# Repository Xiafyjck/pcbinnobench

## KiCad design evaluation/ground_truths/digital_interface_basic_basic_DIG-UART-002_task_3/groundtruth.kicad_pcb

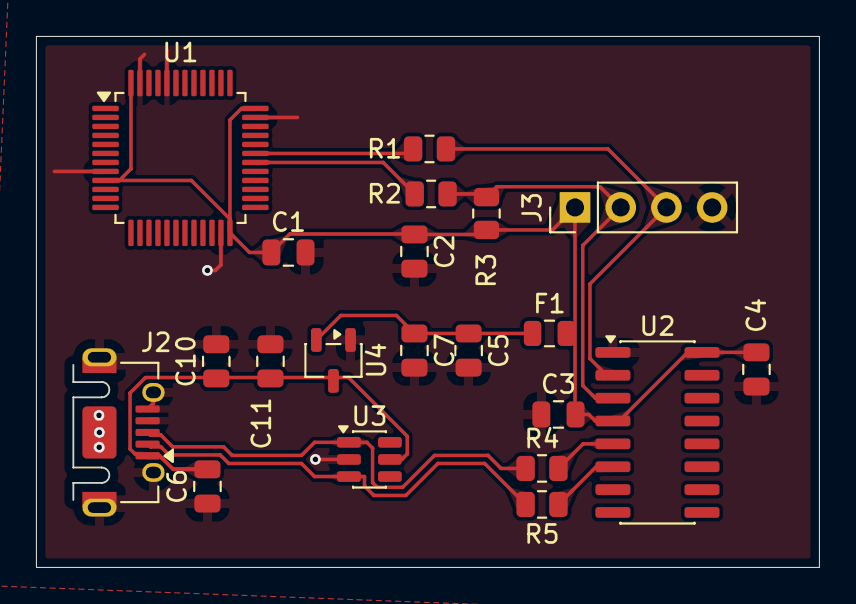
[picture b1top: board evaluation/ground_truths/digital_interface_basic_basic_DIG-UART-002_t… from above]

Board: 2 copper layers, 43.5 x 29.5 mm, 21 parts (0 on the bottom side), 12 nets.

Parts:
C1: 0.1uf; C_0805_2012Metric
C2: 1uf; C_0805_2012Metric
C3, C4, C7, C11: 100nf; C_0805_2012Metric
C5, C6, C10: 10uf; C_0805_2012Metric
F1: Polyfuse; Fuse_0805_2012Metric
J2: USB_B_Micro; USB_Micro-AB_Molex_47590-0001
J3: Conn_01x04_Pin; PinHeader_1x04_P2.54mm_Vertical
R1, R2: 50; R_0805_2012Metric
R3: 10k; R_0805_2012Metric
R4, R5: 22; R_0805_2012Metric
U1: STM32F103C8Tx; LQFP-48_7x7mm_P0.5mm
U2: CH340C; SOIC-16_3.9x9.9mm_P1.27mm
U3: SRV05-4; SOT-23-6
U4: XC6206PxxxMR; SOT-23-3

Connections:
+3V3: C1.1, C2.1, C3.2, C4.2, F1.2, J3.1, R3.2, U1.9 (VDDA), U1.24 (VDD), U1.36 (VDD), U1.48 (VDD), U2.4 (V3), U2.16 (VCC)
+5V: C6.2, C10.1, C11.1, J2.1 (VBUS), U3.5 (VP), U4.3 (VI)
/usb-uart/D+: J2.3 (D+), R4.1, U3.1 (IO1)
/usb-uart/D-: J2.2 (D-), R5.2, U3.3 (IO2)
/usb-uart/RX: J3.2, R2.2, R3.1, U2.3 (RXD)
/usb-uart/TX: J3.3, R1.2, U2.2 (TXD)
GND: C1.2, C2.2, C3.1, C4.1, C5.2, C6.1, C7.2, C10.2, C11.2, J2.4 (ID), J2.5 (GND), J2.6 (Shield), J3.4, U1.8 (VSSA), U1.23 (VSS), U1.35 (VSS), U1.44 (BOOT0), U1.47 (VSS), U2.1 (GND), U3.2 (VN), U4.1 (GND)
unnamed: R2.1, U1.30 (PA9)
unnamed: R1.1, U1.31 (PA10)
unnamed: R4.2, U2.5 (UD+)
unnamed: R5.1, U2.6 (UD-)
unnamed: C5.1, C7.1, F1.1, U4.2 (VO)

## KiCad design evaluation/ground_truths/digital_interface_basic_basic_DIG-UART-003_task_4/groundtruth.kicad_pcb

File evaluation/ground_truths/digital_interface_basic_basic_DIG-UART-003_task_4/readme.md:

# Cross-Voltage Domain UART Interface Board

This directory contains KiCad reference project, datasheets, and fault localization tasks for the cross-voltage domain UART interface board.

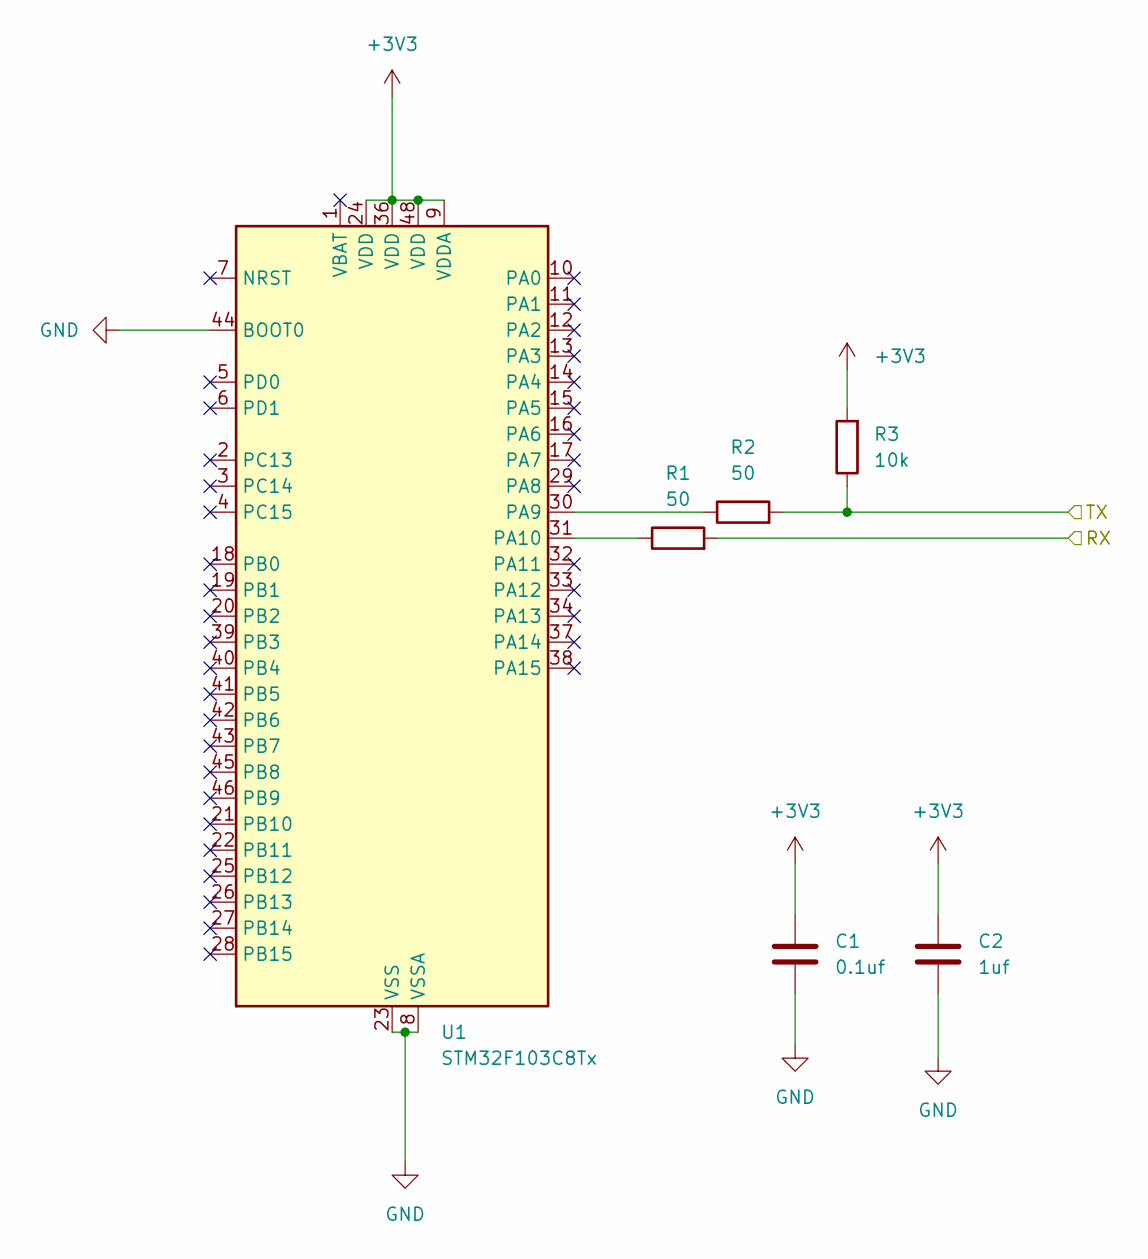
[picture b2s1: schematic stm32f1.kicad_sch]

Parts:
C1: 0.1uf; C_0805_2012Metric
C2: 1uf; C_0805_2012Metric
R1, R2: 50; R_0805_2012Metric
R3: 10k; R_0805_2012Metric
U1: STM32F103C8Tx; LQFP-48_7x7mm_P0.5mm

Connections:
+3V3: C1.1, C2.1, R3.2, U1.9 (VDDA), U1.24 (VDD), U1.36 (VDD), U1.48 (VDD); also elsewhere on the board
/stm32-uart/RX: R1.2; also elsewhere on the board
/stm32-uart/TX: R2.2, R3.1; also elsewhere on the board
GND: C1.2, C2.2, U1.8 (VSSA), U1.23 (VSS), U1.35 (VSS), U1.44 (BOOT0), U1.47 (VSS); also elsewhere on the board
unnamed: R2.1, U1.30 (PA9)
unnamed: R1.1, U1.31 (PA10)

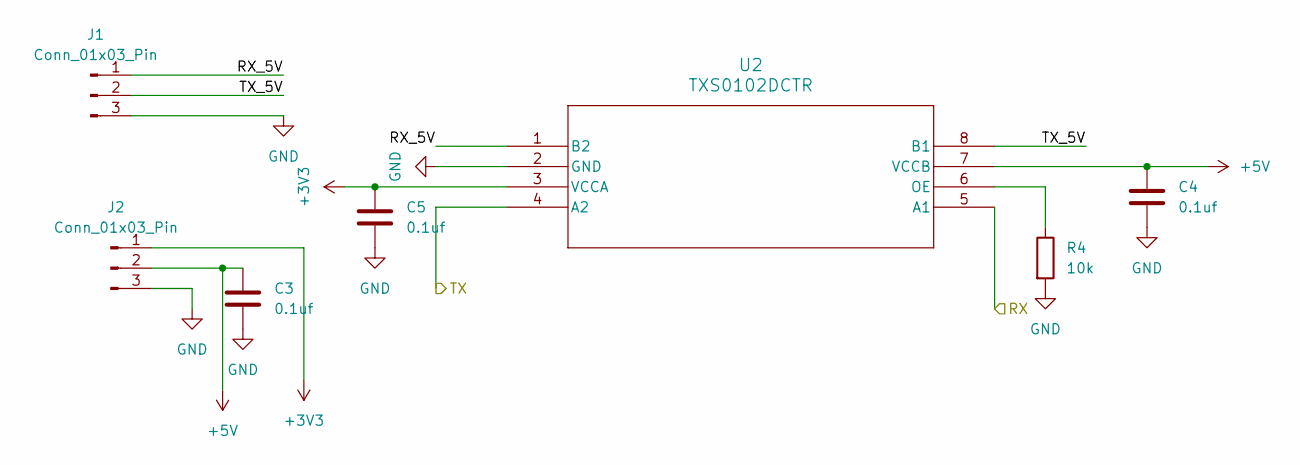
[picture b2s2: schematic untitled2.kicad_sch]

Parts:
C3, C4, C5: 0.1uf; C_0805_2012Metric
J1, J2: Conn_01x03_Pin; PinHeader_1x03_P2.54mm_Vertical
R4: 10k; R_0805_2012Metric
U2: TXS0102DCTR; DCT8

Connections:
+3V3: C5.1, J2.1, U2.3 (VCCA); also elsewhere on the board
+5V: C3.1, C4.1, J2.2, U2.7 (VCCB)
/stm32-uart/RX: U2.4 (A2); also elsewhere on the board
/stm32-uart/TX: U2.5 (A1); also elsewhere on the board
/usb-uart/RX_5V: J1.1, U2.1 (B2)
/usb-uart/TX_5V: J1.2, U2.8 (B1)
GND: C3.2, C4.2, C5.2, J1.3, J2.3, R4.2, U2.2 (GND); also elsewhere on the board
unnamed: R4.1, U2.6 (OE)

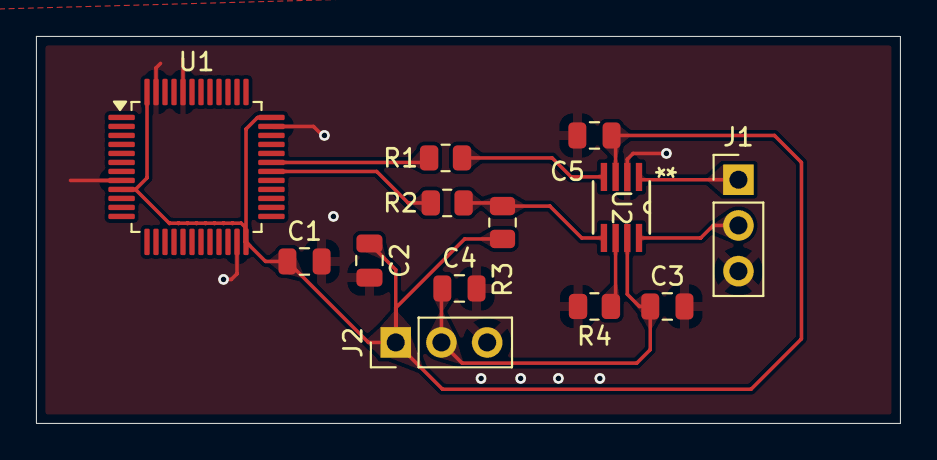
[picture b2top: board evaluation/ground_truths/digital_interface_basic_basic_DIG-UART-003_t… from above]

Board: 2 copper layers, 48.0 x 21.5 mm, 13 parts (0 on the bottom side), 10 nets.

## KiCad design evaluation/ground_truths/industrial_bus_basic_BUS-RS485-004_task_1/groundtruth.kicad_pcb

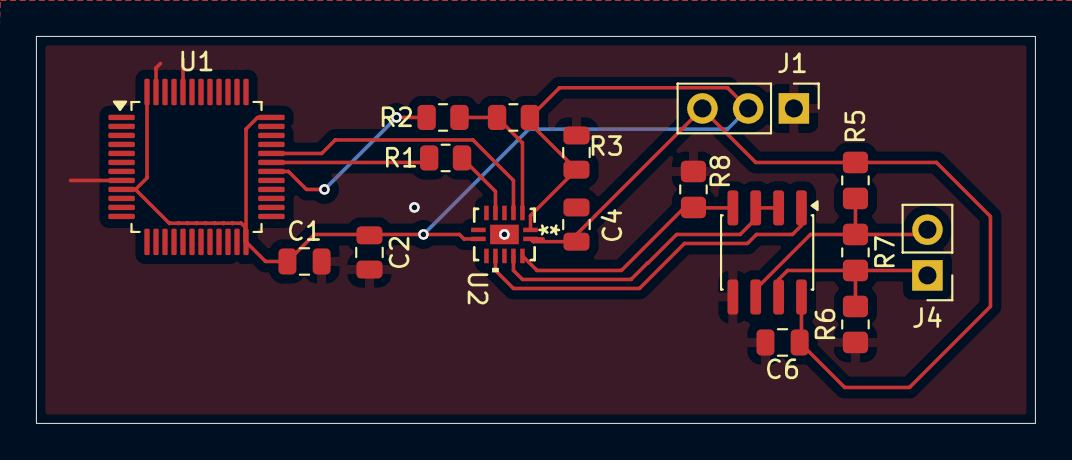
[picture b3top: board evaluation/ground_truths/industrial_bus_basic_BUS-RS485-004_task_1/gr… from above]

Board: 2 copper layers, 55.5 x 21.5 mm, 17 parts (0 on the bottom side), 13 nets.

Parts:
C1, C4, C5: 0.1uf; C_0805_2012Metric
C2: 1uf; C_0805_2012Metric
C6: 2.2uf; C_0805_2012Metric
J1: Conn_01x03_Pin; PinHeader_1x03_P2.54mm_Vertical
J4: Conn_01x02_Pin; PinHeader_1x02_P2.54mm_Vertical
R1, R2: 50; R_0805_2012Metric
R3: 10k; R_0805_2012Metric
R5, R6: 7.4K; R_0805_2012Metric_Pad1.20x1.40mm_HandSolder
R7: 120; R_0805_2012Metric_Pad1.20x1.40mm_HandSolder
R8: 4.7K; R_0805_2012Metric_Pad1.20x1.40mm_HandSolder
U1: STM32F103C8Tx; LQFP-48_7x7mm_P0.5mm
U2: TXU0304BQAR; QFN_04BQAR_TEX
U3: MAX485E; SOIC-8_3.9x4.9mm_P1.27mm

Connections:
+3V3: C1.1, C2.1, C5.1, J1.2, R3.2, U1.9 (VDDA), U1.24 (VDD), U1.36 (VDD), U1.48 (VDD), U2.1 (VCCA), U2.8 (OE)
+5V: C4.1, C6.2, J1.3, R5.2, U2.14 (VCCB), U3.8 (VCC)
/RS485_5V/RS485_2A: J4.2, R5.1, R7.1, U3.6 (A)
/RS485_5V/RS485_2B: J4.1, R6.2, R7.2, U3.7 (B)
/RS485_5V/RS485_2_DE: U2.12 (B2Y), U3.2 (~RE), U3.3 (DE)
/RS485_5V/RS485_2_RX: U2.10 (B4), U3.1 (RO)
/RS485_5V/RS485_2_TX: R8.2, U2.13 (B1Y), U3.4 (DI)
/stm32-uart/DE: U1.32 (PA11), U2.3 (A2)
/stm32-uart/RX: R1.2, U2.5 (A4Y)
/stm32-uart/TX: R2.2, R3.1, U2.2 (A1)
GND: C1.2, C2.2, C4.2, C5.2, C6.1, J1.1, R6.1, R8.1, U1.8 (VSSA), U1.23 (VSS), U1.35 (VSS), U1.44 (BOOT0), U1.47 (VSS), U2.7 (GND), U2.15 (EPAD), U3.5 (GND)
unnamed: R2.1, U1.30 (PA9)
unnamed: R1.1, U1.31 (PA10)

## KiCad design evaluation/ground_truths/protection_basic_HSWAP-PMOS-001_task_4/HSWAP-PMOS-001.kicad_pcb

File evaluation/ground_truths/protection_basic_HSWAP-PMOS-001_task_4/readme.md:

# HSWAP-PMOS-001

Use PMOS for reverse polarity protection. Zener diode here is used for PMOS Vgs, value less than Vgs.

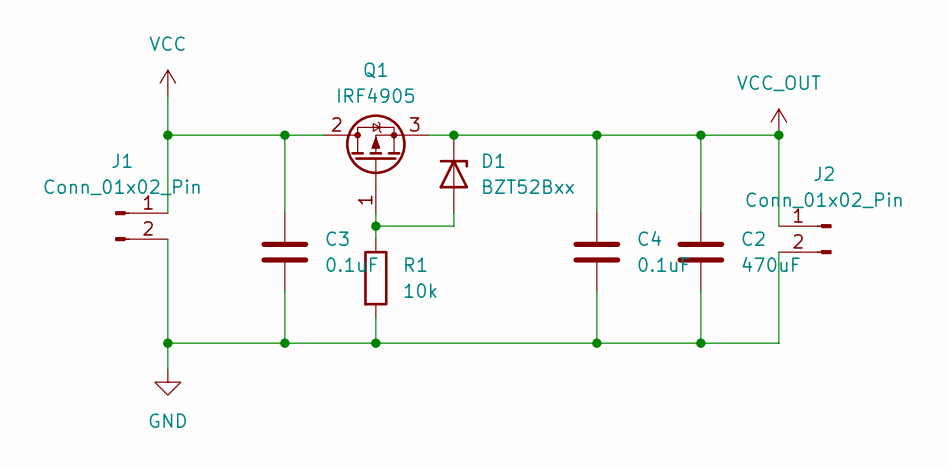
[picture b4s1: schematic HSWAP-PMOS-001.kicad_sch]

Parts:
C2: 470uF; C_Disc_D7.5mm_W5.0mm_P10.00mm
C3, C4: 0.1uF; C_0805_2012Metric
D1: BZT52Bxx; D_SOD-123F
J1, J2: Conn_01x02_Pin; JST_NV_B02P-NV_1x02_P5.00mm_Vertical
Q1: IRF4905; TO-220-3_Vertical
R1: 10k; R_0805_2012Metric

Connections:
GND: C2.2, C3.2, C4.2, J1.2, J2.2, R1.2
unnamed: D1.2 (A), Q1.1 (G), R1.1
VCC: C3.1, J1.1, Q1.2 (D)
VCC_OUT: C2.1, C4.1, D1.1 (K), J2.1, Q1.3 (S)

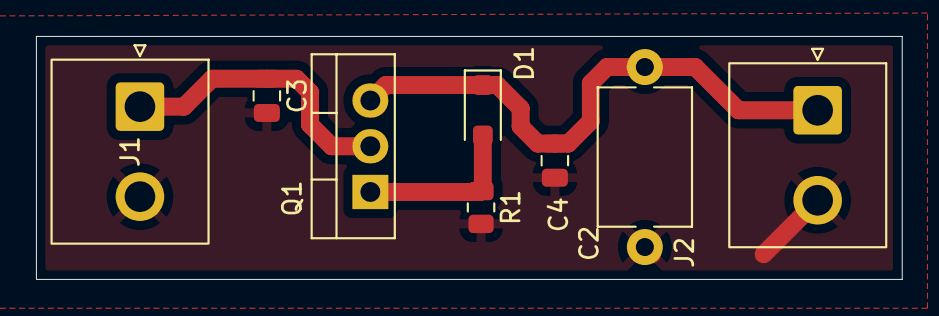
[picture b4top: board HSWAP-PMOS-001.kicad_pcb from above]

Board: 2 copper layers, 48.1 x 13.5 mm, 8 parts (0 on the bottom side), 4 nets.

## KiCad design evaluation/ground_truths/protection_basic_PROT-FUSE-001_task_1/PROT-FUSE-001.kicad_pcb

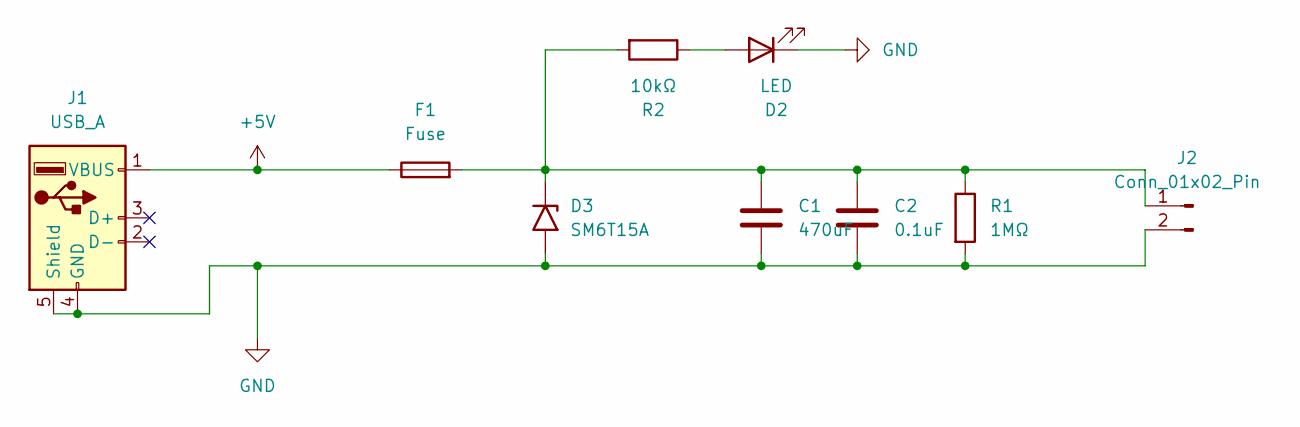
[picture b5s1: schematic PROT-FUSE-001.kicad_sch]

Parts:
C1: 470uF; C_Disc_D9.0mm_W5.0mm_P10.00mm
C2: 0.1uF; C_0805_2012Metric
D2: LED; LED_0805_2012Metric
D3: SM6T15A; D_SMB
F1: Fuse; Fuse_1210_3225Metric
J1: USB_A; USB_A_TE_292303-7_Horizontal
J2: Conn_01x02_Pin; JST_EH_B2B-EH-A_1x02_P2.50mm_Vertical
R1: 1MΩ; R_0805_2012Metric
R2: 10kΩ; R_0805_2012Metric

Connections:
+5V: F1.1, J1.1 (VBUS)
GND: C1.2, C2.2, D2.1 (K), D3.2 (A2), J1.4 (GND), J1.5 (Shield), J2.2, R1.2
unnamed: D2.2 (A), R2.1
unnamed: C1.1, C2.1, D3.1 (A1), F1.2, J2.1, R1.1, R2.2

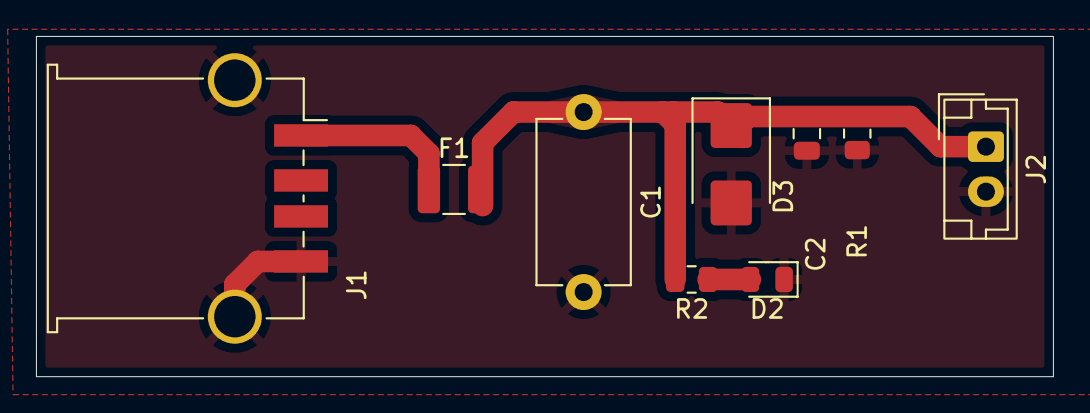
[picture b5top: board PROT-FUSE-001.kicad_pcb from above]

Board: 2 copper layers, 56.5 x 18.9 mm, 9 parts (0 on the bottom side), 4 nets.

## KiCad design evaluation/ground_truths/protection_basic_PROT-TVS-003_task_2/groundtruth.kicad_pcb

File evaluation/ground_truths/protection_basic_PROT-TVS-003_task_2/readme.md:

# PROT-TVS-003

CAN Bus TVS Protection Board for protecting CANH/CANL bus. Design should focus on CAN-specific TVS, optional termination, interface protection location, ground return, and impact on bus communication.

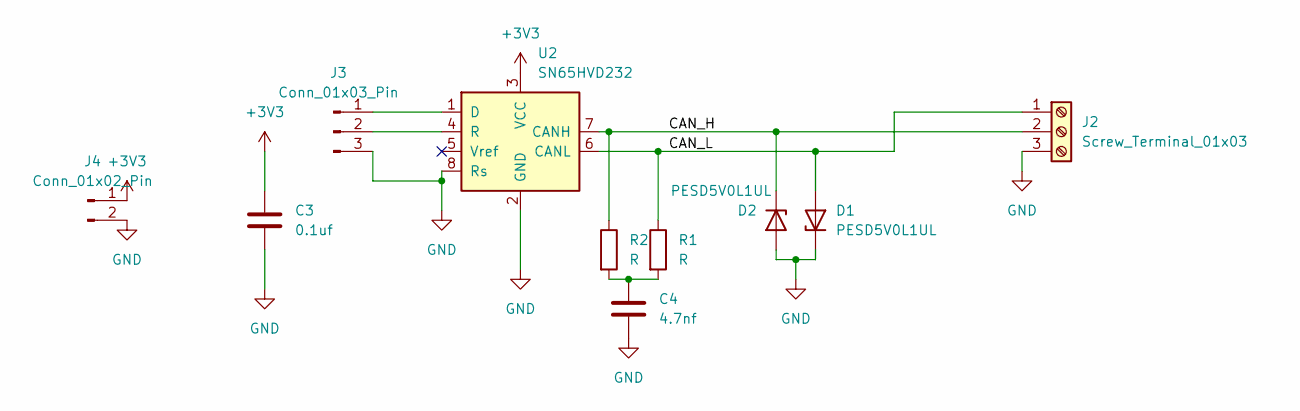
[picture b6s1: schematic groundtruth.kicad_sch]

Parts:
C3: 0.1uf; C_0805_2012Metric
C4: 4.7nf; C_0805_2012Metric
D1, D2: PESD5V0L1UL; D_SOD-882
J2: Screw_Terminal_01x03; TerminalBlock_MaiXu_MX126-5.0-03P_1x03_P5.00mm
J3: Conn_01x03_Pin; PinHeader_1x03_P2.54mm_Vertical
J4: Conn_01x02_Pin; PinHeader_1x02_P2.54mm_Vertical
R1, R2: R; R_0805_2012Metric_Pad1.20x1.40mm_HandSolder
U2: SN65HVD232; SOIC-8_3.9x4.9mm_P1.27mm

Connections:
+3V3: C3.1, J4.1, U2.3 (VCC)
/CAN_H: D2.1 (K), J2.2, R2.1, U2.7 (CANH)
/CAN_L: D1.2 (A), J2.1, R1.1, U2.6 (CANL)
GND: C3.2, C4.2, D1.1 (K), D2.2 (A), J2.3, J3.3, J4.2, U2.2 (GND), U2.8 (Rs)
unnamed: C4.1, R1.2, R2.2
unnamed: J3.1, U2.1 (D)
unnamed: J3.2, U2.4 (R)

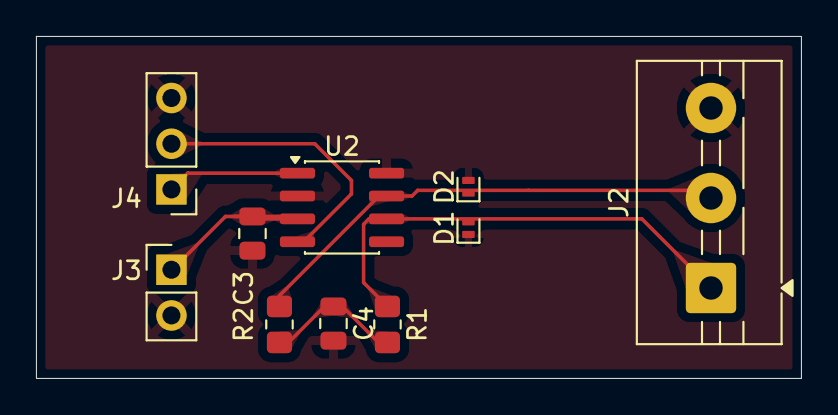
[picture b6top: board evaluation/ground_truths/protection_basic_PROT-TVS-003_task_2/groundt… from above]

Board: 2 copper layers, 42.5 x 19.0 mm, 10 parts (0 on the bottom side), 7 nets.
